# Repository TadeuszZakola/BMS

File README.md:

#Battery Management System  🔋⚡️

Welcome to the Battery Management System (BMS) project! 🚀 This open-source project combines cutting-edge hardware and software to deliver a robust, customizable solution for managing battery packs in applications like electric vehicles. With advanced monitoring, safety features, and seamless integration, this BMS ensures optimal battery performance and longevity. 🌱

🌟 Key Features

26 Individual Cell-Group Voltage Measurements ✅: Monitors voltage across 26 cell groups with high precision.

16 Temperature Sensors 🌡️: Provides comprehensive thermal monitoring to prevent overheating and ensure safe operation.

Cell Balancing 🔄: Actively balances cells to optimize capacity and extend battery lifespan.

Safety Relay 🔒: Isolates the battery pack during faults for enhanced safety.

Current Sensor ⚡: Enables real-time current monitoring and protection against overcurrent conditions.

CAN Bus 📊: Supports CAN communication for integration with external systems and data logging.

Advanced Safety Features 🛡️:

Over-voltage and under-voltage protection

Over-temperature shutdown

Current limiting via relay and BMS logic

Emergency cut-off for driver safety

Hardware & Software Integration 🛠️: Combines robust hardware (microcontroller, sensors, relays) with modular software for real-time monitoring and control.

User-Friendly Dashboard App 🖥️: Visualize battery metrics and configure settings through an intuitive interface.

CAN Integration: Supports CAN bus protocols for data transmission and external control.

Logging: Stores historical data for diagnostics and performance analysis.

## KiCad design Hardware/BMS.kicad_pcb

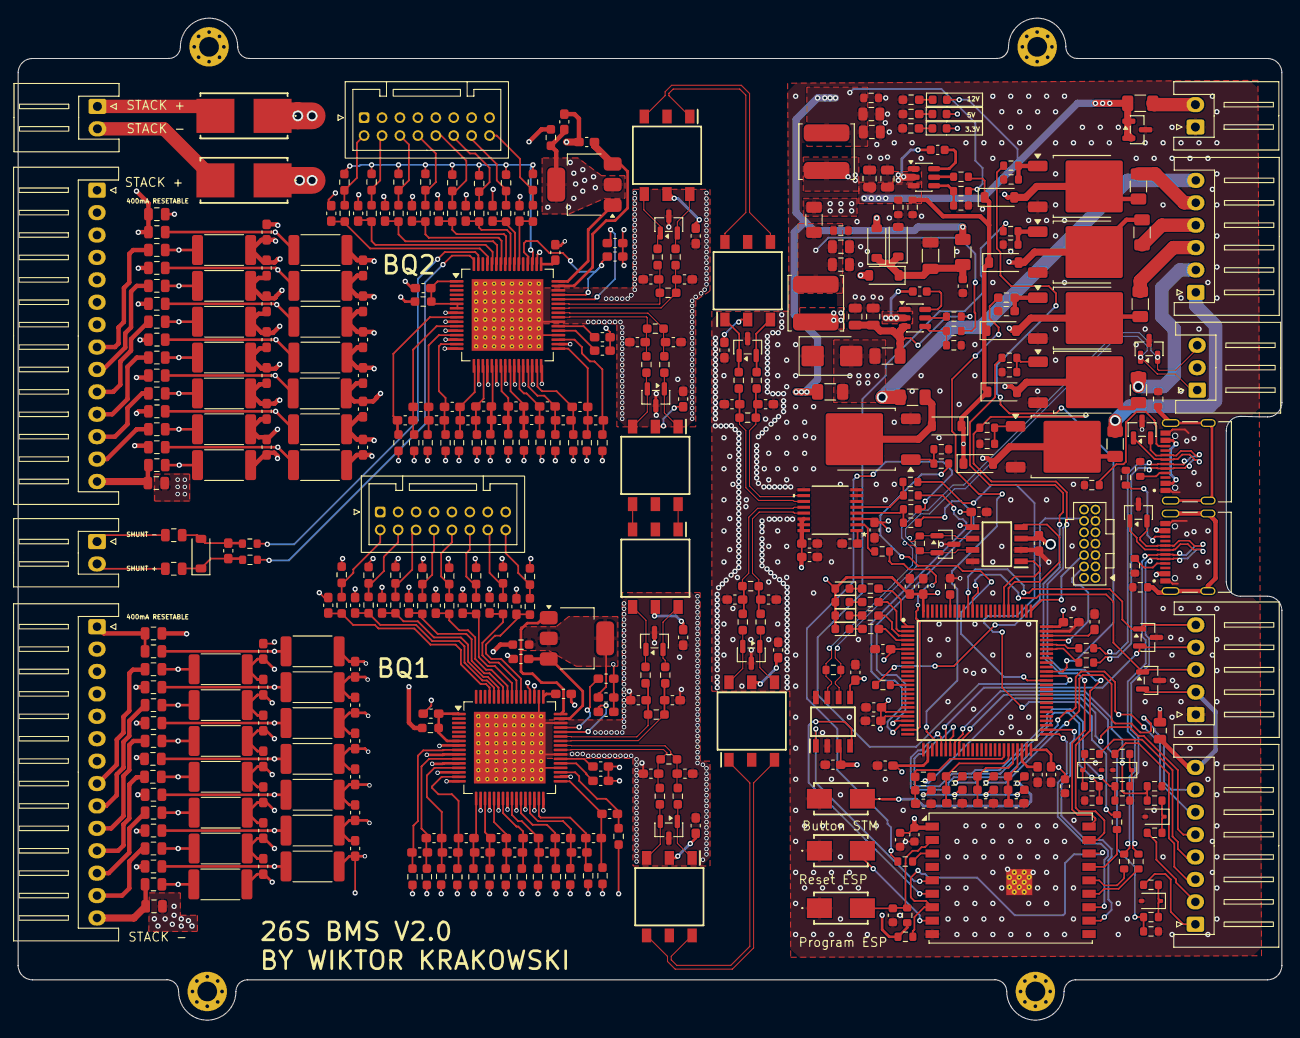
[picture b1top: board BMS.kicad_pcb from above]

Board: 4 copper layers, 141.0 x 111.8 mm, 454 parts (0 on the bottom side), 333 nets.

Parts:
C1: 100n ceramiczny; C_0603_1608Metric_Pad1.08x0.95mm_HandSolder
C2, C51: 0.22uF; C_0603_1608Metric_Pad1.08x0.95mm_HandSolder
C3, C9, C52, C58: 0.1uF; C_0603_1608Metric_Pad1.08x0.95mm_HandSolder
C4, C53: 10nF; C_0603_1608Metric_Pad1.08x0.95mm_HandSolder
C5, C8, C42, C43, C44, C45, C46, C48, C49, C50, C54, C57, C66, C72, C73, C74, C75, C76, C77, C78, C79: 1uF; C_0603_1608Metric_Pad1.08x0.95mm_HandSolder
C6, C55: 4.7uF; C_0603_1608Metric_Pad1.08x0.95mm_HandSolder
C7, C56: 2.2uF; C_0603_1608Metric_Pad1.08x0.95mm_HandSolder
C10, C11, C14, C15, C59, C60, C63, C64, C113, C129, C132, C133, C146, C149, C150, C151, C152, C153: 220p; C_0603_1608Metric_Pad1.08x0.95mm_HandSolder
C16, C17, C18, C19, C20, C21, C22, C23, C24, C25, C26, C27, C28, C29, C30, C31, C32, C33, C34, C35, C36, C37, C38, C39, C40, C41, C80, C81, C82, C83, C84, C85, C86, C87, C88, C89, C90, C91, C92, C93, C94, C95, C96, C97, C98, C99, C100, C101, C102, C103, C104, C105, C145: 0.47uF; C_0603_1608Metric_Pad1.08x0.95mm_HandSolder
C65, C67, C68, C69, C70: 100n; C_0603_1608Metric_Pad1.08x0.95mm_HandSolder
C106, C110, C111, C112, C114: 0.1u; C_0603_1608Metric_Pad1.08x0.95mm_HandSolder
C107, C108: 0.22u; C_0603_1608Metric_Pad1.08x0.95mm_HandSolder
C109: 0.1uF 50V; C_0603_1608Metric_Pad1.08x0.95mm_HandSolder
C116, C117, C147, C148: 100nF; C_0603_1608Metric_Pad1.08x0.95mm_HandSolder
C121, C122: 100n 280mOhm; C_0603_1608Metric
C125: 1uF; C_0603_1608Metric
C126: 22u; C_1206_3216Metric
C130, C131, C136, C154, C155, C157, C160, C161: 22u; C_0805_2012Metric
C134, C135, C137, C156: 1uF; R_0603_1608Metric
C138, C142, C143, C144: 100nF; C_0603_1608Metric
C139, C140: 2.2n; C_0603_1608Metric_Pad1.08x0.95mm_HandSolder
C141: 47n; C_0603_1608Metric_Pad1.08x0.95mm_HandSolder
D1, D8, D11, D13, D19, D20, D21, D22, D23: 60V/0.5/3A; D_SOD-123
D2, D3, D4, D5, D10, D14, D18: LED; LED_0603_1608Metric
D9: 6V; D_SOD-123
D17: P6SMB6.8CA/TR13; D_SMB
D27, D28, D29, D30: 12V; D_SOD-323
D33, D34, D35, D36, D37, D38, D39, D40, D41, D42, D43, D44, D45: 13.3V tvs; SOT-23
F1, F7, F8, F9, F10, F11, F12, F13, F14, F15, F16, F17, F18, F19, F20, F21, F22, F23, F24, F25, F26, F27, F28, F29, F30, F31, F32, F33, F34, F35, F36, F37, F45, F46, F55: 400mA; Fuse_0805_2012Metric
F2, F5, F38, F39: 1A; Fuse_1206_3216Metric
F3: 3A; Fuse_1206_3216Metric
F6, F48, F49, F50, F51, F52: 1A 24V; Fuse_1206_3216Metric
F53, F54: 01550900M
H1, H2, H3, H4: MountingHole; MountingHole_2.2mm_M2_Pad_Via
IC1: STM32H742VIT6
IC2, IC3: TPS563200DDCR; SOT-23-6
J1, J11: Conn_01x02; JST_XH_S2B-XH-A_1x02_P2.50mm_Horizontal
J7: FTSH-107-01-L-D-K; FTSH-107-XX-YYY-D-K
J12, J13: TYPE-C-31-M-12; HRO_TYPE-C-31-M-12
J14, J15: Conn_01x14; JST_XH_S14B-XH-A_1x14_P2.50mm_Horizontal
J17: S2B-XH-A(LF)(SN); JST_XH_S2B-XH-A_1x02_P2.50mm_Horizontal
J19, J25: B16B-PUDSS-1(LF)(SN); JST_PUD_B16B-PUDSS_2x08_P2.00mm_Vertical
J21: S6B-XH-A-1(LF)(SN); JST_XH_S6B-XH-A_1x06_P2.50mm_Horizontal
J22: S3B-XH-A(LF)(SN); JST_XH_S3B-XH-A_1x03_P2.50mm_Horizontal
J23: S8B-XH-A(LF)(SN); JST_XH_S8B-XH-A_1x08_P2.50mm_Horizontal
J24: S5B-XH-A(LF)(SN); JST_XH_S5B-XH-A_1x05_P2.50mm_Horizontal
L1: 4.7u; L_TDK_VLS6045EX_VLS6045AF
L2: 3.3u; L_TDK_VLS6045EX_VLS6045AF
Q1, Q3, Q4, Q5, Q6, Q7: STD3NK90ZT4; TO-252-2
Q2, Q8: 100V/2W; SOT-223-3_TabPin2
R1: 100k; R_0603_1608Metric_Pad0.98x0.95mm_HandSolder
R2, R64: 300; R_0603_1608Metric_Pad0.98x0.95mm_HandSolder
R3, R58, R62, R132, R134: 100; R_0603_1608Metric
R4, R66: 30; R_0603_1608Metric_Pad0.98x0.95mm_HandSolder
R5, R8, R9, R10, R11, R12, R18, R50, R51, R52, R57, R67, R70, R74, R95, R96, R97, R98, R99, R106, R107, R108, R151, R152, R153, R154, R155, R162: 1k; R_0603_1608Metric_Pad0.98x0.95mm_HandSolder
R6, R7, R13, R16, R60, R63, R65, R68, R69, R71, R72, R73: 49; R_0603_1608Metric_Pad0.98x0.95mm_HandSolder
R14, R17, R47, R48, R49, R53, R54, R55, R100, R102, R103, R104, R105, R109, R110, R111, R146, R150, R157, R159: 10k; R_0603_1608Metric_Pad0.98x0.95mm_HandSolder
R15, R61: 300R; R_0603_1608Metric
R19, R20, R21, R22, R23, R24, R25, R26, R27, R28, R29, R30, R31, R32, R112, R113, R114, R115, R116, R117, R118, R119, R120, R121, R122, R123, R124, R125, R161: 100; R_0603_1608Metric_Pad0.98x0.95mm_HandSolder
R33, R34, R35, R36, R37, R38, R39, R40, R41, R42, R43, R44, R45, R46, R77, R78, R79, R80, R81, R82, R83, R84, R85, R86, R87, R88, R89, R90: 20R 2W; R_2512_6332Metric
R56, R59, R131, R133, R135, R168, R169, R170, R172, R173, R179: 10k; R_0603_1608Metric
R75, R76, R101, R126: 5.1K; R_0603_1608Metric
R91, R92, R93, R94, R127, R128, R129, R130: 0R; R_0603_1608Metric
R145, R149, R156, R158: 500; R_0603_1608Metric_Pad0.98x0.95mm_HandSolder
R160, R185, R188, R191: 500; R_0603_1608Metric
R163: 4.7k; R_0603_1608Metric_Pad0.98x0.95mm_HandSolder
R164: 3k; R_0603_1608Metric_Pad0.98x0.95mm_HandSolder
R165: 54.9k; R_0603_1608Metric
R166, R183, R186, R189: 15k; R_0603_1608Metric
R167: 33.2; R_0603_1608Metric
R171, R174: 1M; R_0603_1608Metric
R175, R176, R177, R178: 33; R_0603_1608Metric
R180, R181: 120R; R_0603_1608Metric
R182, R184, R187, R190: 5.6k; R_0603_1608Metric
SW1, SW2, SW3: SW_Push; 1478732
T3, T4, T5, T6, T7, T8: SM91502ALE; SOP254P927X572-6N
U1, U2: BQ79614PAPRQ1; Texas_TQFP-64-1EP_10x10mm_P0.5mm_EP8x8mm_Mask4.44x4.44mm_Th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
U3: PBQ79600PWQ1; BQ79600-Q1
U4, U6: MCP2542FD-E/MF; SOIC127P600X175-8N
U5: ESP32-C3-WROOM-02U

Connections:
5V_USB: C125.2, C126.2, D9.1 (K), D19.1 (K), D20.1 (K), F38.1
12V_IN: F3.1, J17.2
+3.3V: C1.2, C65.2, C66.1, C67.2, C68.1, C69.1, C70.1, C106.1, C116.2, C138.2, C141.2, C142.2, C143.2, C147.2, D2.2 (A), D3.2 (A), D4.2 (A), D5.2 (A), D14.2 (A), F5.2, IC1.6 (VBAT), IC1.20 (VREF+), IC1.21 (VDDA), IC1.27 (VDD_2), IC1.50 (VDD_3), IC1.75 (VDD_4), IC1.100 (VDD_5), J7.3, R146.1, R150.1, R157.1, R159.1, R172.2, R173.2, U3.3 (VIO), U4.5 (VIO), U5.1 (3V3), U6.5 (VIO)
+5V: C108.1, C109.1, C117.1, C148.1, D10.2 (A), D17.2 (A2), F2.2, F39.1, U3.14 (CVDD), U3.15 (BAT), U3.16 (INH), U4.3 (VDD), U6.3 (VDD)
+12V: C134.1, C135.1, C155.1, C157.1, D1.1 (K), D8.1 (K), D13.1 (K), D18.2 (A), D21.1 (K), D22.1 (K), D23.1 (K), D44.1 (A1), D44.2 (A2), F3.2, F55.2, IC2.3 (VIN), R170.2
/12V_Enable: IC1.29 (PA5), R161.1
/Analog_Input1: IC1.30 (PA6), R166.1, R182.2
/Analog_Input2: IC1.32 (PC4), R183.1, R184.2
/Analog_Input3: IC1.33 (PC5), R186.1, R187.2
/Analog_Input4: IC1.34 (PB0), R189.1, R190.2
/Button1: C110.2, IC1.47 (PB11), R145.2, R146.2
/Button2: C111.2, IC1.46 (PB10), R149.2, R150.2
/Button3: C112.2, IC1.45 (PE15), R156.2, R157.2
/Button4: C114.2, IC1.44 (PE14), R158.2, R159.2
/CAN_RX: IC1.81 (PD0), U4.4 (RXD)
/CAN_TX: IC1.82 (PD1), U4.1 (TXD)
/Connectivity/5V_fused_minus: F6.2, J21.3
/Connectivity/12V_Analog_Input1: J23.4, R160.2
/Connectivity/12V_Analog_Input2: J23.3, R185.2
/Connectivity/12V_Analog_Input3: J23.2, R188.2
/Connectivity/12V_Analog_Input4: J23.1, R191.2
/Connectivity/+12V_curr_sense: D33.2 (A2), F55.1, J23.8, J24.2
/Connectivity/B2_IN: J23.7, R149.1
/Connectivity/B3_IN: J23.6, R156.1
/Connectivity/B4_IN: J23.5, R158.1
/Connectivity/D1: D1.2 (A), F49.1, Q1.2 (D)
/Connectivity/D2: D13.2 (A), F48.1, Q3.2 (D)
/Connectivity/D3: D8.2 (A), F6.1, Q4.2 (D)
/Connectivity/EX_CANFD+: D35.2 (A2), D37.2 (A2), J22.3, R180.2, R181.2, U4.7 (CANH), U6.7 (CANH)
/Connectivity/EX_CANFD-: D35.1 (A1), D37.1 (A1), J22.1, R180.1, R181.1, U4.6 (CANL), U6.6 (CANL)
/Connectivity/G1: Q1.1 (G), R3.2, R56.2
/Connectivity/G2: Q3.1 (G), R58.2, R59.2
/Connectivity/PreCharge_OUT: F48.2, J21.5
/Connectivity/Program_esp: C144.2, R173.1, SW3.2, U5.2 (EN)
/Connectivity/Relay_OUT: F49.2, J21.4
/Connectivity/Relay_OUT2: F51.2, J21.2
/Connectivity/Relay_OUT3: F52.2, J21.1
/Connectivity/Relay_OUT4: F50.2, J21.6
/Connectivity/USB1_DN: D34.1 (A1), J12.A7 (DN1), J12.B7 (DN2), R176.2
/Connectivity/USB1_DP: D34.2 (A2), J12.A6 (DP1), J12.B6 (DP2), R175.2
/Connectivity/USB2+: R177.1, U5.14 (IO19)
/Connectivity/USB2-: R178.1, U5.13 (IO18)
/Connectivity/USB2_DN: D36.1 (A1), J13.A7 (DN1), J13.B7 (DN2), R178.2
/Connectivity/USB2_DP: D36.2 (A2), J13.A6 (DP1), J13.B6 (DP2), R177.2
/Connectivity/esp32_can_rx: U5.6 (IO7), U6.4 (RXD)
/Connectivity/esp32_can_tx: U5.5 (IO6), U6.1 (TXD)
/Connectivity/relay_enable1: R62.1, U5.18 (IO0)
/Connectivity/relay_enable2: R132.1, U5.17 (IO1)
/ERROR: IC1.1 (PE2), R154.1
/LED1: IC1.2 (PE3), R153.1
/LED2: IC1.3 (PE4), R152.1
/LED3: IC1.4 (PE5), R151.1
/Mesurements_LTC1/Bat_pin: C4.2, R4.2, U1.1 (BAT), U1.6 (CB14), U1.7 (VC14)
/Mesurements_LTC1/Battery/Batt1_+: F21.2, R2.1, R4.1
/Mesurements_LTC1/CB0: C41.1, R46.2, U1.34 (CB0)
/Mesurements_LTC1/CB1: C40.1, C41.2, R45.2, U1.32 (CB1)
/Mesurements_LTC1/CB2: C39.1, C40.2, R44.2, U1.30 (CB2)
/Mesurements_LTC1/CB3: C38.1, C39.2, R43.2, U1.28 (CB3)
/Mesurements_LTC1/CB4: C37.1, C38.2, R42.2, U1.26 (CB4)
/Mesurements_LTC1/CB5: C36.1, C37.2, R41.2, U1.24 (CB5)
/Mesurements_LTC1/CB6: C35.1, C36.2, R40.2, U1.22 (CB6)
/Mesurements_LTC1/CB7: C34.1, C35.2, R39.2, U1.20 (CB7)
/Mesurements_LTC1/CB8: C33.1, C34.2, R38.2, U1.18 (CB8)
/Mesurements_LTC1/CB9: C32.1, C33.2, R37.2, U1.16 (CB9)
/Mesurements_LTC1/CB10: C31.1, C32.2, R36.2, U1.14 (CB10)
/Mesurements_LTC1/CB11: C30.1, C31.2, R35.2, U1.12 (CB11)
/Mesurements_LTC1/CB12: C29.1, C30.2, R34.2, U1.10 (CB12)
/Mesurements_LTC1/CB13: C29.2, R33.2, U1.8 (CB13)
/Mesurements_LTC1/COMHN: C60.2, R67.2, R71.1, U1.42 (COMHN)
/Mesurements_LTC1/COMHP: C59.2, R67.1, R68.1, U1.43 (COMHP)
/Mesurements_LTC1/COMLN: C133.2, R65.2, R70.2, U1.41 (COMLN)
/Mesurements_LTC1/COMLP: C132.2, R69.2, R70.1, U1.40 (COMLP)
/Mesurements_LTC1/Temperature_LTC_1/T1: C42.1, R8.1, U1.61 (GPIO1)
/Mesurements_LTC1/Temperature_LTC_1/T2: C45.1, R11.1, U1.60 (GPIO2)
/Mesurements_LTC1/Temperature_LTC_1/T3: C46.1, R12.1, U1.59 (GPIO3)
/Mesurements_LTC1/Temperature_LTC_1/T4: C43.1, R9.1, U1.58 (GPIO4)
/Mesurements_LTC1/Temperature_LTC_1/T5: C44.1, R10.1, U1.57 (GPIO5)
/Mesurements_LTC1/Temperature_LTC_1/T6: C48.1, R50.1, U1.56 (GPIO6)
/Mesurements_LTC1/Temperature_LTC_1/T7: C49.1, R51.1, U1.55 (GPIO7)
/Mesurements_LTC1/Temperature_LTC_1/T8: C50.1, R52.1, U1.54 (GPIO8)
/Mesurements_LTC1/Temperature_LTC_1/TSREF: R14.1, R17.2, R47.2, R48.2, R49.2, R53.2, R54.2, R55.2, U1.51 (TSREF)
/Mesurements_LTC1/Temperature_LTC_1/Thermistor1: J19.2, R8.2, R14.2
/Mesurements_LTC1/Temperature_LTC_1/Thermistor2: J19.4, R11.2, R48.1
/Mesurements_LTC1/Temperature_LTC_1/Thermistor3: J19.6, R12.2, R49.1
/Mesurements_LTC1/Temperature_LTC_1/Thermistor4: J19.8, R9.2, R17.1
/Mesurements_LTC1/Temperature_LTC_1/Thermistor5: J19.10, R10.2, R47.1
/Mesurements_LTC1/Temperature_LTC_1/Thermistor6: J19.12, R50.2, R53.1
/Mesurements_LTC1/Temperature_LTC_1/Thermistor7: J19.14, R51.2, R54.1
/Mesurements_LTC1/Temperature_LTC_1/Thermistor8: J19.16, R52.2, R55.1
/Mesurements_LTC1/VC0: C28.1, R19.2, U1.35 (VC0)
/Mesurements_LTC1/VC1: C27.1, C28.2, R32.2, U1.33 (VC1)
/Mesurements_LTC1/VC2: C26.1, C27.2, R31.2, U1.31 (VC2)
/Mesurements_LTC1/VC3: C25.1, C26.2, R30.2, U1.29 (VC3)
/Mesurements_LTC1/VC4: C24.1, C25.2, R29.2, U1.27 (VC4)
/Mesurements_LTC1/VC5: C23.1, C24.2, R28.2, U1.25 (VC5)
/Mesurements_LTC1/VC6: C22.1, C23.2, R27.2, U1.23 (VC6)
/Mesurements_LTC1/VC7: C21.1, C22.2, R26.2, U1.21 (VC7)
/Mesurements_LTC1/VC8: C20.1, C21.2, R25.2, U1.19 (VC8)
/Mesurements_LTC1/VC9: C19.1, C20.2, R24.2, U1.17 (VC9)
/Mesurements_LTC1/VC10: C18.1, C19.2, R23.2, U1.15 (VC10)
/Mesurements_LTC1/VC11: C17.1, C18.2, R22.2, U1.13 (VC11)
/Mesurements_LTC1/VC12: C16.1, C17.2, R21.2, U1.11 (VC12)
/Mesurements_LTC1/VC13: C16.2, R20.2, U1.9 (VC13)
/Mesurements_LTC1/to_rx: C6.2, U1.45 (CVDD), U1.52 (RX)
/Mesurements_LTC2/Battery2/Batt2_+: F23.2, R64.1, R66.1
/Mesurements_LTC2/CB0: C105.1, R90.2, U2.34 (CB0)
/Mesurements_LTC2/CB1: C104.1, C105.2, R89.2, U2.32 (CB1)
/Mesurements_LTC2/CB2: C103.1, C104.2, R88.2, U2.30 (CB2)
/Mesurements_LTC2/CB3: C102.1, C103.2, R87.2, U2.28 (CB3)
/Mesurements_LTC2/CB4: C101.1, C102.2, R86.2, U2.26 (CB4)
/Mesurements_LTC2/CB5: C100.1, C101.2, R85.2, U2.24 (CB5)
/Mesurements_LTC2/CB6: C99.1, C100.2, R84.2, U2.22 (CB6)
/Mesurements_LTC2/CB7: C98.1, C99.2, R83.2, U2.20 (CB7)
/Mesurements_LTC2/CB8: C97.1, C98.2, R82.2, U2.18 (CB8)
/Mesurements_LTC2/CB9: C96.1, C97.2, R81.2, U2.16 (CB9)
/Mesurements_LTC2/CB10: C95.1, C96.2, R80.2, U2.14 (CB10)
/Mesurements_LTC2/CB11: C94.1, C95.2, R79.2, U2.12 (CB11)
/Mesurements_LTC2/CB12: C93.1, C94.2, R78.2, U2.10 (CB12)
/Mesurements_LTC2/CB13: C93.2, R77.2, U2.8 (CB13)
/Mesurements_LTC2/COMHN: C129.2, R57.2, R63.1, U2.42 (COMHN)
/Mesurements_LTC2/COMHP: C113.2, R57.1, R60.1, U2.43 (COMHP)
/Mesurements_LTC2/COMLN: C15.2, R13.2, R18.2, U2.41 (COMLN)
/Mesurements_LTC2/COMLP: C14.2, R16.2, R18.1, U2.40 (COMLP)
/Mesurements_LTC2/Temperature_LTC_2/T1: C72.1, R95.1, U2.61 (GPIO1)
/Mesurements_LTC2/Temperature_LTC_2/T2: C75.1, R98.1, U2.60 (GPIO2)
/Mesurements_LTC2/Temperature_LTC_2/T3: C76.1, R99.1, U2.59 (GPIO3)
/Mesurements_LTC2/Temperature_LTC_2/T4: C73.1, R96.1, U2.58 (GPIO4)
/Mesurements_LTC2/Temperature_LTC_2/T5: C74.1, R97.1, U2.57 (GPIO5)
/Mesurements_LTC2/Temperature_LTC_2/T6: C77.1, R106.1, U2.56 (GPIO6)
/Mesurements_LTC2/Temperature_LTC_2/T7: C78.1, R107.1, U2.55 (GPIO7)
/Mesurements_LTC2/Temperature_LTC_2/T8: C79.1, R108.1, U2.54 (GPIO8)
/Mesurements_LTC2/Temperature_LTC_2/TSREF: R100.1, R102.2, R103.2, R104.2, R105.2, R109.2, R110.2, R111.2, U2.51 (TSREF)
/Mesurements_LTC2/Temperature_LTC_2/Thermistor1: J25.2, R95.2, R100.2
/Mesurements_LTC2/Temperature_LTC_2/Thermistor2: J25.4, R98.2, R104.1
/Mesurements_LTC2/Temperature_LTC_2/Thermistor3: J25.6, R99.2, R105.1
/Mesurements_LTC2/Temperature_LTC_2/Thermistor4: J25.8, R96.2, R102.1
/Mesurements_LTC2/Temperature_LTC_2/Thermistor5: J25.10, R97.2, R103.1
/Mesurements_LTC2/Temperature_LTC_2/Thermistor6: J25.12, R106.2, R109.1
/Mesurements_LTC2/Temperature_LTC_2/Thermistor7: J25.14, R107.2, R110.1
/Mesurements_LTC2/Temperature_LTC_2/Thermistor8: J25.16, R108.2, R111.1
/Mesurements_LTC2/VC0: C92.1, R112.2, U2.35 (VC0)
/Mesurements_LTC2/VC1: C91.1, C92.2, R125.2, U2.33 (VC1)
/Mesurements_LTC2/VC2: C90.1, C91.2, R124.2, U2.31 (VC2)
/Mesurements_LTC2/VC3: C89.1, C90.2, R123.2, U2.29 (VC3)
/Mesurements_LTC2/VC4: C88.1, C89.2, R122.2, U2.27 (VC4)
/Mesurements_LTC2/VC5: C87.1, C88.2, R121.2, U2.25 (VC5)
/Mesurements_LTC2/VC6: C86.1, C87.2, R120.2, U2.23 (VC6)
/Mesurements_LTC2/VC7: C85.1, C86.2, R119.2, U2.21 (VC7)
/Mesurements_LTC2/VC8: C84.1, C85.2, R118.2, U2.19 (VC8)
/Mesurements_LTC2/VC9: C83.1, C84.2, R117.2, U2.17 (VC9)
/Mesurements_LTC2/VC10: C82.1, C83.2, R116.2, U2.15 (VC10)
/Mesurements_LTC2/VC11: C81.1, C82.2, R115.2, U2.13 (VC11)
/Mesurements_LTC2/VC12: C80.1, C81.2, R114.2, U2.11 (VC12)
/Mesurements_LTC2/VC13: C80.2, R113.2, U2.9 (VC13)
/Mesurements_LTC2/to_rx: C55.2, U2.45 (CVDD), U2.52 (RX)
/NFAULT: IC1.24 (PA2), R93.2
/NRST: J7.12, R94.2
/Power/5V/5V_unfused: C136.1, C154.1, C156.1, F2.1, F38.2, L1.2, R165.2
/Power/Power_3.3V/3.3V_unfused: C130.1, C131.1, C137.1, F5.1, L2.2, R167.2
/RX_1: IC1.23 (PA1), R91.2
/SIGNAL_PRECHARGE: IC1.65 (PC8), R58.1
/SIGNAL_RELAY: IC1.64 (PC7), R3.1
/SIGNAL_RELAY2: IC1.63 (PC6), R134.1
/SPI_CLK: D33.1 (A1), IC1.89 (PB3), J24.3
/SPI_MISO: D45.1 (A1), IC1.90 (PB4), J24.5
/SPI_MOSI: D45.2 (A2), IC1.31 (PA7), J24.4
/STM Comunication Interface/COMHN: C11.2, R5.2, R7.1, U3.12 (COMHN)
/STM Comunication Interface/COMHP: C10.2, R5.1, R6.1, U3.13 (COMHP)
/STM Comunication Interface/COMLN: C64.2, R72.2, R74.2, U3.11 (COMLN)
/STM Comunication Interface/COMLP: C63.2, R73.2, R74.1, U3.10 (COMLP)
/STM Comunication Interface/MISO/TX: R91.1, R127.1, U3.5 (MISO/TX)
/STM Comunication Interface/MOSI/RX: R92.1, R128.1, U3.4 (MOSI/RX)
/STM Comunication Interface/NFAULT: R93.1, U3.2 (NFAULT)
/SWCLK: IC1.76 (PA14), J7.6
/SWDIO: IC1.72 (PA13), J7.4
/TX_1: IC1.22 (PA0), R92.2
/UART2_RX: IC1.51 (PB12), U5.12 (IO21/TXD)
/UART2_TX: IC1.52 (PB13), U5.11 (IO20/RXD)
/USB+: IC1.71 (PA12), R175.1
/USB-: IC1.70 (PA11), R176.1
/esp32_RX2: R127.2, R129.2
/esp32_TX2: R128.2, R130.2
/galvanic_isulation_0/S1+: D42.1 (A1), R68.2, T3.4 (SEC_1)
/galvanic_isulation_0/S1-: D42.2 (A2), R71.2, T3.6 (SEC_3)
/galvanic_isulation_0/S2+: T3.3 (PRI_3), T4.4 (SEC_1)
/galvanic_isulation_0/S2-: T3.1 (PRI_1), T4.6 (SEC_3)
/galvanic_isulation_0/S3+: D43.2 (A2), R73.1, T4.3 (PRI_3)
/galvanic_isulation_0/S3-: D43.1 (A1), R72.1, T4.1 (PRI_1)
/galvanic_isulation_1/S1+: D38.1 (A1), R60.2, T5.4 (SEC_1)
/galvanic_isulation_1/S1-: D38.2 (A2), R63.2, T5.6 (SEC_3)
/galvanic_isulation_1/S2+: T5.3 (PRI_3), T6.4 (SEC_1)
/galvanic_isulation_1/S2-: T5.1 (PRI_1), T6.6 (SEC_3)
/galvanic_isulation_1/S3+: D39.2 (A2), R69.1, T6.3 (PRI_3)
/galvanic_isulation_1/S3-: D39.1 (A1), R65.1, T6.1 (PRI_1)
/galvanic_isulation_2/S1+: D40.1 (A1), R6.2, T7.4 (SEC_1)
/galvanic_isulation_2/S1-: D40.2 (A2), R7.2, T7.6 (SEC_3)
/galvanic_isulation_2/S2+: T7.3 (PRI_3), T8.4 (SEC_1)
/galvanic_isulation_2/S2-: T7.1 (PRI_1), T8.6 (SEC_3)
/galvanic_isulation_2/S3+: D41.2 (A2), R16.1, T8.3 (PRI_3)
/galvanic_isulation_2/S3-: D41.1 (A1), R13.1, T8.1 (PRI_1)
Batt_Coupling: C2.1, C3.1, C4.1, C5.1, C6.1, C7.1, C8.1, C9.1, C42.2, C43.2, C44.2, C45.2, C46.2, C48.2, C49.2, C50.2, C59.1, C60.1, C132.1, C133.1, C146.2, C150.2, D39.3 (common), D42.3 (common), F20.2, J19.1, J19.3, J19.5, J19.7, J19.9, J19.11, J19.13, J19.15, U1.36 (REFHM), U1.39 (AVSS), U1.46 (CVSS), U1.50 (DVSS), U1.65 (PAD)
GND: C1.1, C10.1, C11.1, C63.1, C64.1, C65.1, C66.2, C67.1, C68.2, C69.2, C70.2, C106.2, C107.1, C108.2, C109.2, C110.1, C111.1, C112.1, C114.1, C116.1, C117.2, C125.1, C126.1, C130.2, C131.2, C134.2, C135.2, C136.2, C137.2, C138.1, C139.1, C140.1, C141.1, C142.1, C143.1, C144.1, C147.1, C148.2, C149.2, C152.1, C154.2, C155.2, C156.2, C157.2, C160.2, C161.2, D9.2 (A), D17.1 (A1), D27.2 (A), D28.2 (A), D29.2 (A), D30.2 (A), D33.3 (common), D34.3 (common), D35.3 (common), D36.3 (common), D37.3 (common), D40.3 (common), D43.3 (common), D44.3 (common), D45.3 (common), IC1.19 (VSSA), IC1.26 (VSS_2), IC1.49 (VSS_3), IC1.74 (VSS_4), IC1.99 (VSS_5), IC2.1 (GND), IC3.1 (GND), J7.5, J7.7, J7.11, J12.A1_B12 (GND), J12.B1_A12 (GND), J13.A1_B12 (GND), J13.B1_A12 (GND), J17.1, J24.1, Q1.3 (S), Q3.3 (S), Q4.3 (S), Q5.3 (S), Q6.3 (S), Q7.3 (S), R1.1, R56.1, R59.1, R75.1, R76.2, R101.2, R126.1, R131.1, R133.1, R135.1, R155.1, R162.1, R163.1, R164.1, R168.1, R169.1, R171.1, R174.1, R182.1, R184.1, R187.1, R190.1, SW1.2, SW2.1, SW3.1, U3.6 (SCLK), U3.7 (nCS), U3.8 (nUART/SPI(SPI_RDY)), U3.9 (GND), U4.2 (VSS), U4.8 (STBY), U5.9 (GND), U5.19 (GND), U6.2 (VSS), U6.8 (STBY)
GND_HV2: C14.1, C15.1, C51.1, C52.1, C53.1, C54.1, C55.1, C56.1, C57.1, C58.1, C72.2, C73.2, C74.2, C75.2, C76.2, C77.2, C78.2, C79.2, C113.1, C129.1, C151.1, C153.2, D38.3 (common), D41.3 (common), F22.2, J25.1, J25.3, J25.5, J25.7, J25.9, J25.11, J25.13, J25.15, U2.36 (REFHM), U2.39 (AVSS), U2.46 (CVSS), U2.50 (DVSS), U2.65 (PAD)
unnamed: D2.1 (K), R151.2
unnamed: D3.1 (K), R152.2
unnamed: D4.1 (K), R153.2
unnamed: D5.1 (K), R154.2
unnamed: D10.1 (K), R155.2
unnamed: C145.1, D11.2 (A), F46.2, R61.2
unnamed: C145.2, D11.1 (K), F45.2, R15.2
unnamed: D14.1 (K), R162.2
unnamed: D18.1 (K), R164.2
unnamed: D19.2 (A), J13.A4_B9 (VBUS), J13.B4_A9 (VBUS)
unnamed: D20.2 (A), J12.A4_B9 (VBUS), J12.B4_A9 (VBUS)
unnamed: D21.2 (A), F51.1, Q5.2 (D)
unnamed: D22.2 (A), F52.1, Q6.2 (D)
unnamed: D23.2 (A), F50.1, Q7.2 (D)
unnamed: D27.1 (K), R160.1, R166.2
unnamed: D28.1 (K), R183.2, R185.1
unnamed: D29.1 (K), R186.2, R188.1
unnamed: D30.1 (K), R189.2, R191.1
unnamed: F1.2, R20.1, R33.1
unnamed: F7.2, R21.1, R34.1
unnamed: F8.2, R22.1, R35.1
unnamed: F9.2, R23.1, R36.1
unnamed: F10.2, R24.1, R37.1
unnamed: F11.2, R25.1, R38.1
unnamed: F12.2, R26.1, R39.1
unnamed: F13.2, R27.1, R40.1
unnamed: F14.2, R28.1, R41.1
unnamed: F15.2, R29.1, R42.1
unnamed: F16.2, R30.1, R43.1
unnamed: F17.2, R31.1, R44.1
unnamed: F18.2, R32.1, R45.1
unnamed: F19.2, R19.1, R46.1
unnamed: F24.2, R77.1, R113.1
unnamed: F25.2, R78.1, R114.1
unnamed: F26.2, R79.1, R115.1
unnamed: F27.2, R80.1, R116.1
unnamed: F28.2, R81.1, R117.1
unnamed: F29.2, R82.1, R118.1
unnamed: F30.2, R83.1, R119.1
unnamed: F31.2, R84.1, R120.1
unnamed: F32.2, R85.1, R121.1
unnamed: F33.2, R86.1, R122.1
unnamed: F34.2, R87.1, R123.1
unnamed: F35.2, R88.1, R124.1
unnamed: F36.2, R89.1, R125.1
unnamed: F37.2, R90.1, R112.1
unnamed: IC1.94 (BOOT0), R1.2
unnamed: IC1.14 (NRST), R94.1
unnamed: C139.2, IC1.48 (VCAP_1)
unnamed: C140.2, IC1.73 (VCAP_2)
unnamed: IC2.5 (EN), R170.1
unnamed: C121.2, IC2.2 (SW), L1.1
unnamed: C121.1, IC2.6 (VBST)
unnamed: IC2.4 (VFB), R165.1, R169.2
unnamed: IC3.5 (EN), R179.1
unnamed: C122.2, IC3.2 (SW), L2.1
unnamed: C122.1, IC3.6 (VBST)
unnamed: IC3.4 (VFB), R167.1, R168.2
unnamed: C160.1, C161.1, F39.2, IC3.3 (VIN), R179.2
unnamed: F53.2, J1.1
unnamed: F54.2, J1.2
unnamed: F46.1, J11.1
unnamed: F45.1, J11.2
unnamed: J12.A5 (CC1), R76.1
unnamed: J12.B5 (CC2), R75.2
unnamed: J12.S1 (SHIELD), J12.S2 (SHIELD), J12.S3 (SHIELD), J12.S4 (SHIELD), R174.2
unnamed: J13.A5 (CC1), R101.1
unnamed: J13.B5 (CC2), R126.2
unnamed: J13.S1 (SHIELD), J13.S2 (SHIELD), J13.S3 (SHIELD), J13.S4 (SHIELD), R171.2
unnamed: F7.1, J14.2
unnamed: F8.1, J14.3
unnamed: F9.1, J14.4
unnamed: F10.1, J14.5
unnamed: F11.1, J14.6
unnamed: F12.1, J14.7
unnamed: F13.1, J14.8
unnamed: F14.1, J14.9
unnamed: F15.1, J14.10
unnamed: F16.1, J14.11
unnamed: F17.1, J14.12
unnamed: F18.1, J14.13
unnamed: F19.1, F20.1, J14.14
unnamed: F23.1, F24.1, J15.1
unnamed: F25.1, J15.2
unnamed: F26.1, J15.3
unnamed: F27.1, J15.4
unnamed: F28.1, J15.5
unnamed: F29.1, J15.6
unnamed: F30.1, J15.7
unnamed: F31.1, J15.8
unnamed: F32.1, J15.9
unnamed: F33.1, J15.10
unnamed: F34.1, J15.11
unnamed: F35.1, J15.12
unnamed: F36.1, J15.13
unnamed: Q2.1 (B), U2.48 (NPNB)
unnamed: C51.2, Q2.2 (C), R64.2
unnamed: C52.2, Q2.3 (E), U2.47 (LDOIN)
unnamed: Q4.1 (G), R161.2, R163.2
unnamed: Q5.1 (G), R62.2, R131.2
unnamed: Q6.1 (G), R132.2, R133.2
unnamed: Q7.1 (G), R134.2, R135.2
unnamed: Q8.1 (B), U1.48 (NPNB)
unnamed: C2.2, Q8.2 (C), R2.2
unnamed: C3.2, Q8.3 (E), U1.47 (LDOIN)
unnamed: R145.1, SW1.1
unnamed: C146.1, T3.5 (SEC_2)
unnamed: C149.1, T4.2 (PRI_2)
unnamed: C151.2, T5.5 (SEC_2)
unnamed: C150.1, T6.2 (PRI_2)
unnamed: C152.2, T7.5 (SEC_2)
unnamed: C153.1, T8.2 (PRI_2)
unnamed: C5.2, U1.38 (AVDD)
unnamed: R61.1, U1.63 (BBN)
unnamed: R15.1, U1.64 (BBP)
unnamed: C7.2, U1.49 (DVDD)
unnamed: C9.2, U1.44 (NEG5V)
unnamed: C8.2, U1.37 (REFHP)
unnamed: C54.2, U2.38 (AVDD)
unnamed: C53.2, R66.2, U2.1 (BAT), U2.7 (VC14)
unnamed: C56.2, U2.49 (DVDD)
unnamed: C58.2, U2.44 (NEG5V)
unnamed: C57.2, U2.37 (REFHP)
unnamed: C107.2, U3.1 (DVDD)
unnamed: R172.1, U5.7 (IO8), U5.16 (IO2)
unnamed: R129.1, U5.15 (IO3)
unnamed: R130.1, U5.3 (IO4)
unnamed: SW2.2, U5.8 (IO9)
Stack+: F1.1, F21.1, F53.1, J14.1
Stack-: F22.1, F37.1, F54.1, J15.14

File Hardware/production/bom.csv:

Designator,Footprint,Quantity,Value,LCSC Part #
C1,0603,1,100n ceramiczny,
"C10, C11, C113, C129, C132, C133, C14, C146, C149, C15, C150, C151, C152, C153, C59, C60, C63, C64",0603,18,220p,
"C100, C101, C102, C103, C104, C105, C145, C16, C17, C18, C19, C20, C21, C22, C23, C24, C25, C26, C27, C28, C29, C30, C31, C32, C33, C34, C35, C36, C37, C38, C39, C40, C41, C80, C81, C82, C83, C84, C85, C86, C87, C88, C89, C90, C91, C92, C93, C94, C95, C96, C97, C98, C99",0603,53,0.47uF,
"C106, C110, C111, C112, C114",0603,5,0.1u,
"C107, C108",0603,2,0.22u,
C109,0603,1,0.1uF 50V,
"C116, C117, C138, C142, C143, C144, C147, C148",0603,8,100nF,
"C121, C122",0603,2,100n 280mOhm,
"C125, C134, C135, C137, C156, C42, C43, C44, C45, C46, C48, C49, C5, C50, C54, C57, C66, C72, C73, C74, C75, C76, C77, C78, C79, C8",0603,26,1uF,
C126,1206,1,22u,
"C130, C131, C136, C154, C155, C157, C160, C161",0805,8,22u,
"C139, C140",0603,2,2.2n,
C141,0603,1,47n,
"C2, C51",0603,2,0.22uF,
"C3, C52, C58, C9",0603,4,0.1uF,
"C4, C53",0603,2,10nF,
"C55, C6",0603,2,4.7uF,
"C56, C7",0603,2,2.2uF,
"C65, C67, C68, C69, C70",0603,5,100n,
"D1, D11, D13, D19, D20, D21, D22, D23, D8",D_SOD-123,9,60V/0.5/3A,
"D10, D14, D18, D2, D3, D4, D5",0603,7,LED,
D17,D_SMB,1,P6SMB6.8CA/TR13,
"D27, D28, D29, D30",D_SOD-323,4,12V,
"D33, D34, D35, D36, D37, D38, D39, D40, D41, D42, D43, D44, D45",SOT-23,13,13.3V tvs,
D9,D_SOD-123,1,6V,
"F1, F10, F11, F12, F13, F14, F15, F16, F17, F18, F19, F20, F21, F22, F23, F24, F25, F26, F27, F28, F29, F30, F31, F32, F33, F34, F35, F36, F37, F45, F46, F55, F7, F8, F9",0805,35,400mA,
"F2, F38, F39, F5",1206,4,1A,
F3,1206,1,3A,
"F48, F49, F50, F51, F52, F6",1206,6,1A 24V,
"F53, F54",01550900M,2,01550900M,
"H1, H2, H3, H4",MountingHole_2.2mm_M2_Pad_Via,4,MountingHole,
IC1,STM32H742VIT6,1,STM32H742VIT6,
"IC2, IC3",SOT-23-6,2,TPS563200DDCR,
"J1, J11",JST_XH_S2B-XH-A_1x02_P2.50mm_Horizontal,2,Conn_01x02,
"J12, J13",HRO_TYPE-C-31-M-12,2,TYPE-C-31-M-12,
"J14, J15",JST_XH_S14B-XH-A_1x14_P2.50mm_Horizontal,2,Conn_01x14,
J17,JST_XH_S2B-XH-A_1x02_P2.50mm_Horizontal,1,S2B-XH-A(LF)(SN),
"J19, J25",JST_PUD_B16B-PUDSS_2x08_P2.00mm_Vertical,2,B16B-PUDSS-1(LF)(SN),
J21,JST_XH_S6B-XH-A_1x06_P2.50mm_Horizontal,1,S6B-XH-A-1(LF)(SN),
J22,JST_XH_S3B-XH-A_1x03_P2.50mm_Horizontal,1,S3B-XH-A(LF)(SN),
J23,JST_XH_S8B-XH-A_1x08_P2.50mm_Horizontal,1,S8B-XH-A(LF)(SN),
J24,JST_XH_S5B-XH-A_1x05_P2.50mm_Horizontal,1,S5B-XH-A(LF)(SN),
J7,FTSH-107-XX-YYY-D-K,1,FTSH-107-01-L-D-K,
L1,L_TDK_VLS6045EX_VLS6045AF,1,4.7u,
L2,L_TDK_VLS6045EX_VLS6045AF,1,3.3u,
"Q1, Q3, Q4, Q5, Q6, Q7",TO-252-2,6,STD3NK90ZT4,
"Q2, Q8",SOT-223-3_TabPin2,2,100V/2W,
R1,0603,1,100k,
"R10, R106, R107, R108, R11, R12, R151, R152, R153, R154, R155, R162, R18, R5, R50, R51, R52, R57, R67, R70, R74, R8, R9, R95, R96, R97, R98, R99",0603,28,1k,
"R100, R102, R103, R104, R105, R109, R110, R111, R131, R133, R135, R14, R146, R150, R157, R159, R168, R169, R17, R170, R172, R173, R179, R47, R48, R49, R53, R54, R55, R56, R59",0603,31,10k,
"R101, R126, R75, R76",0603,4,5.1K,
"R112, R113, R114, R115, R116, R117, R118, R119, R120, R121, R122, R123, R124, R125, R132, R134, R161, R19, R20, R21, R22, R23, R24, R25, R26, R27, R28, R29, R3, R30, R31, R32, R58, R62",0603,34,100,
"R127, R128, R129, R130, R91, R92, R93, R94",0603,8,0R,
"R13, R16, R6, R60, R63, R65, R68, R69, R7, R71, R72, R73",0603,12,49,
"R145, R149, R156, R158, R160, R185, R188, R191",0603,8,500,
"R15, R61",0603,2,300R,
R163,0603,1,4.7k,
R164,0603,1,3k,
R165,0603,1,54.9k,
"R166, R183, R186, R189",0603,4,15k,
R167,0603,1,33.2,
"R171, R174",0603,2,1M,
"R175, R176, R177, R178",0603,4,33,
"R180, R181",0603,2,120R,
"R182, R184, R187, R190",0603,4,5.6k,
"R2, R64",0603,2,300,
"R33, R34, R35, R36, R37, R38, R39, R40, R41, R42, R43, R44, R45, R46, R77, R78, R79, R80, R81, R82, R83, R84, R85, R86, R87, R88, R89, R90",2512,28,20R 2W,
"R4, R66",0603,2,30,
"SW1, SW2, SW3",1478732,3,SW_Push,
"T3, T4, T5, T6, T7, T8",SOP254P927X572-6N,6,SM91502ALE,
"U1, U2",Texas_TQFP-64-1EP_10x10mm_P0.5mm_EP8x8mm_Mask4.44x4.44mm_ThermalVias,2,BQ79614PAPRQ1,
U3,BQ79600-Q1,1,PBQ79600PWQ1,
"U4, U6",SOIC127P600X175-8N,2,MCP2542FD-E/MF,
U5,ESP32-C3-WROOM-02U,1,ESP32-C3-WROOM-02U,

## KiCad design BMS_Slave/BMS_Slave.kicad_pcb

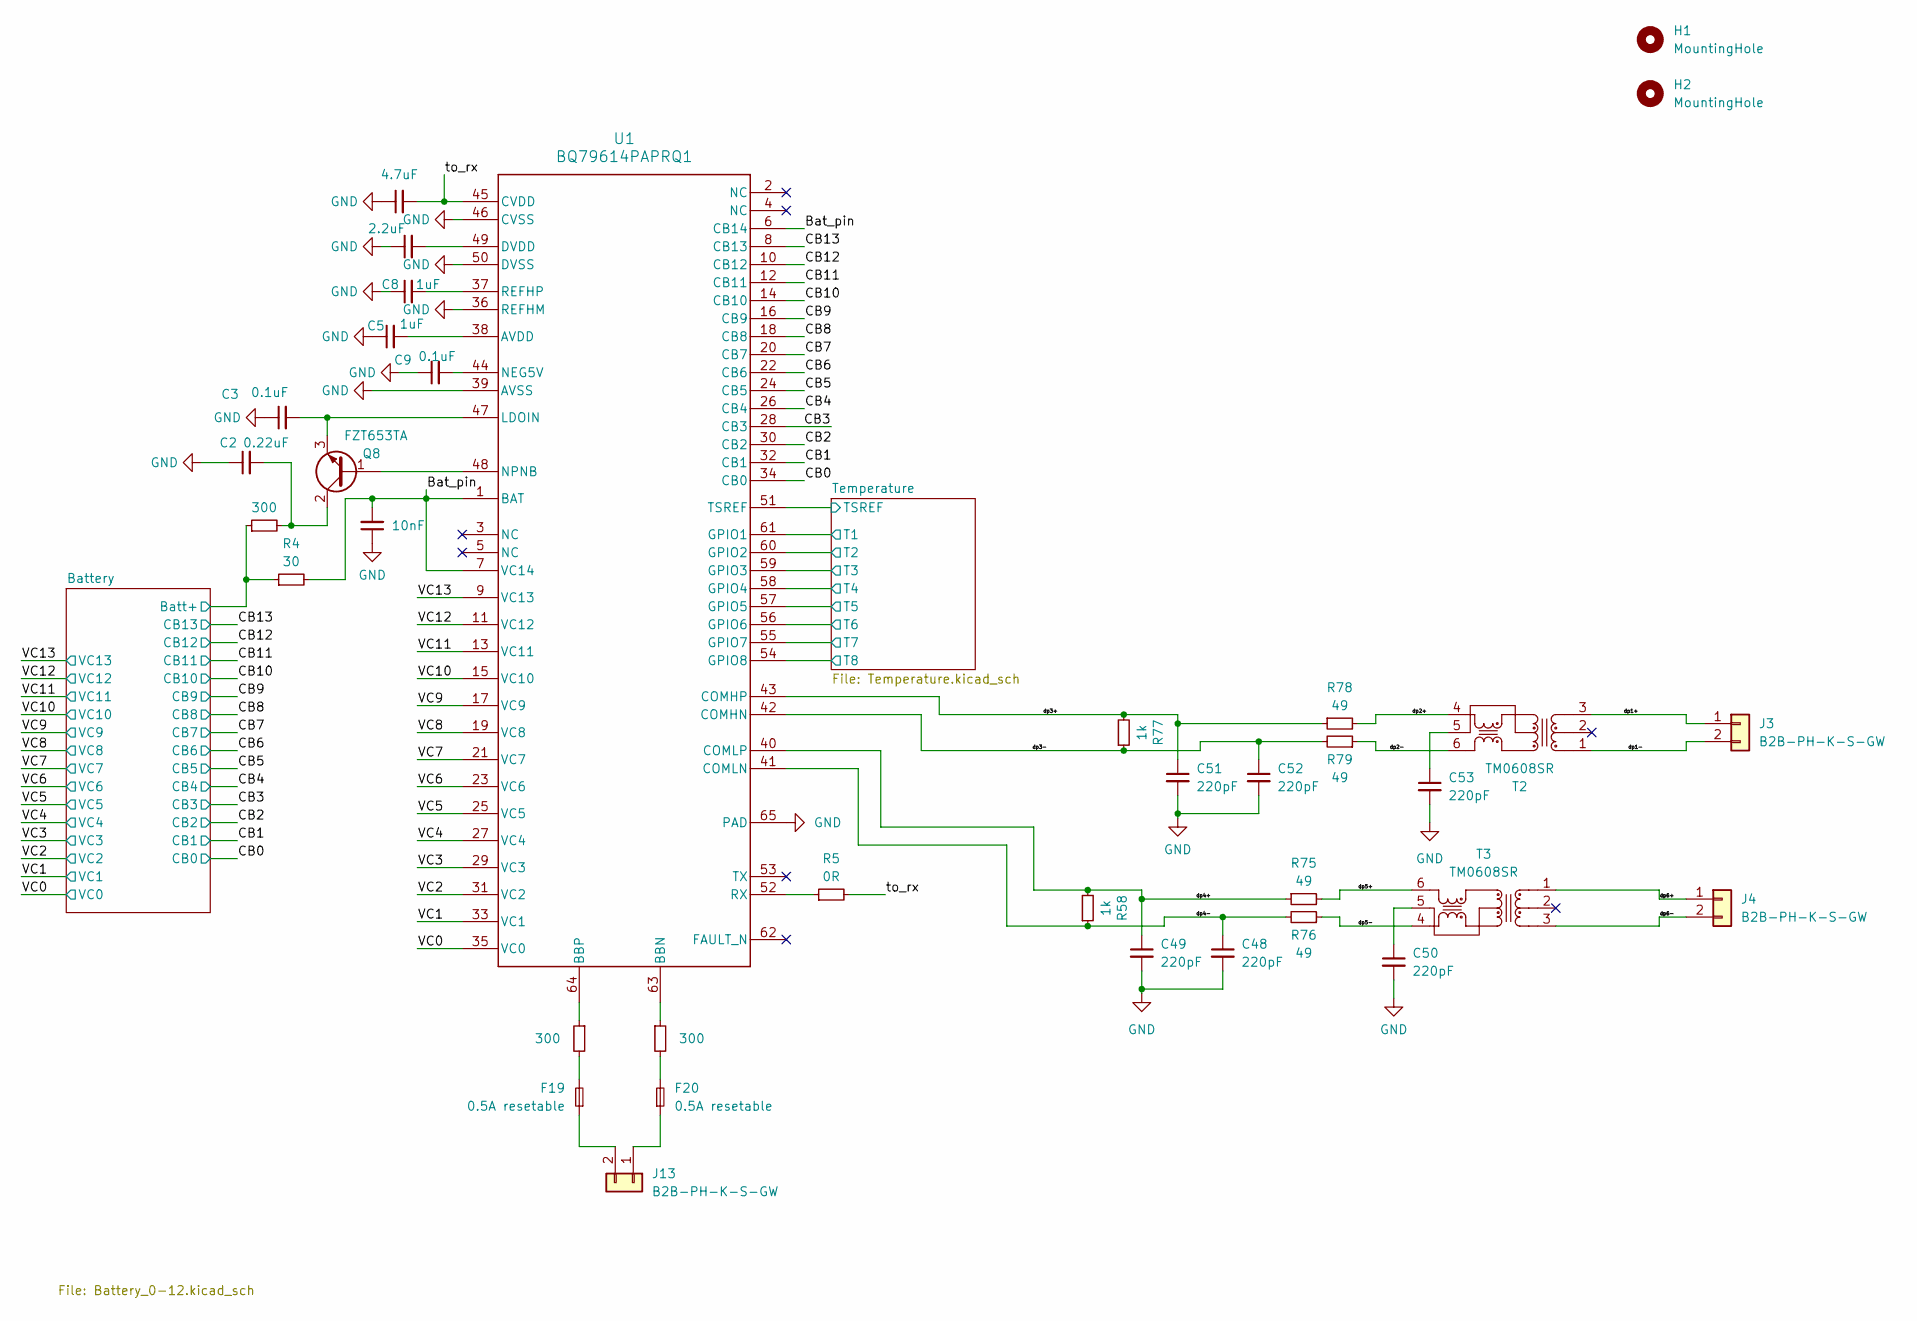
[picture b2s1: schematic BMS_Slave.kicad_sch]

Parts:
C2: 0.22uF; C_0805_2012Metric
C3, C9: 0.1uF; C_0603_1608Metric
C4: 10nF; C_0603_1608Metric_Pad1.08x0.95mm_HandSolder
C5, C8: 1uF; C_0805_2012Metric
C6: 4.7uF; C_0805_2012Metric
C7: 2.2uF; C_0805_2012Metric
C48, C49, C50, C51, C52, C53: 220pF; C_0603_1608Metric; Mouser Part Number 581-06033A221JAT2A
F19, F20: 0.5A resetable; Fuse_0805_2012Metric
H1, H2: MountingHole; MountingHole_3.2mm_M3_DIN965
J3, J4, J13: B2B-PH-K-S-GW; CONN2_B2B-PH-K-S_JST
Q8: FZT653TA; SOT-223-3_TabPin2; Mouser Part Number 522-FZT653TA
R2, R3, R6: 300; R_0603_1608Metric
R4: 30; R_0603_1608Metric
R5: 0R; R_0603_1608Metric
R58, R77: 1k; R_0603_1608Metric; Manufacturer_Part_Number RT0603FRE07330RL; Mouser Part Number --
R75, R76, R78, R79: 49; R_0603_1608Metric; Manufacturer_Part_Number RT0603FRE07330RL; Mouser Part Number 603-RT0603FRE07330RL
T2, T3: TM0608SR; IC6_SM91502ALA-E_BRN; Mouser Part Number 652-SM91502ALE
U1: BQ79614PAPRQ1; Texas_TQFP-64-1EP_10x10mm_P0.5mm_EP8x8mm_Mask4.44x4.44mm_Th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

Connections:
/Bat_pin: C4.2, R4.2, U1.1 (BAT), U1.6 (CB14), U1.7 (VC14)
/Battery/Batt+: R2.1, R4.1; also elsewhere on the board
/CB0: U1.34 (CB0); also elsewhere on the board
/CB1: U1.32 (CB1); also elsewhere on the board
/CB2: U1.30 (CB2); also elsewhere on the board
/CB3: U1.28 (CB3); also elsewhere on the board
/CB4: U1.26 (CB4); also elsewhere on the board
/CB5: U1.24 (CB5); also elsewhere on the board
/CB6: U1.22 (CB6); also elsewhere on the board
/CB7: U1.20 (CB7); also elsewhere on the board
/CB8: U1.18 (CB8); also elsewhere on the board
/CB9: U1.16 (CB9); also elsewhere on the board
/CB10: U1.14 (CB10); also elsewhere on the board
/CB11: U1.12 (CB11); also elsewhere on the board
/CB12: U1.10 (CB12); also elsewhere on the board
/CB13: U1.8 (CB13); also elsewhere on the board
/Temperature/T1: U1.61 (GPIO1); also elsewhere on the board
/Temperature/T2: U1.60 (GPIO2); also elsewhere on the board
/Temperature/T3: U1.59 (GPIO3); also elsewhere on the board
/Temperature/T4: U1.58 (GPIO4); also elsewhere on the board
/Temperature/T5: U1.57 (GPIO5); also elsewhere on the board
/Temperature/T6: U1.56 (GPIO6); also elsewhere on the board
/Temperature/T7: U1.55 (GPIO7); also elsewhere on the board
/Temperature/T8: U1.54 (GPIO8); also elsewhere on the board
/Temperature/TSREF: U1.51 (TSREF); also elsewhere on the board
/VC0: U1.35 (VC0); also elsewhere on the board
/VC1: U1.33 (VC1); also elsewhere on the board
/VC2: U1.31 (VC2); also elsewhere on the board
/VC3: U1.29 (VC3); also elsewhere on the board
/VC4: U1.27 (VC4); also elsewhere on the board
/VC5: U1.25 (VC5); also elsewhere on the board
/VC6: U1.23 (VC6); also elsewhere on the board
/VC7: U1.21 (VC7); also elsewhere on the board
/VC8: U1.19 (VC8); also elsewhere on the board
/VC9: U1.17 (VC9); also elsewhere on the board
/VC10: U1.15 (VC10); also elsewhere on the board
/VC11: U1.13 (VC11); also elsewhere on the board
/VC12: U1.11 (VC12); also elsewhere on the board
/VC13: U1.9 (VC13); also elsewhere on the board
/dp1+: J3.1, T2.3 (PRI_3)
/dp1-: J3.2, T2.1 (PRI_1)
/dp2+: R78.2, T2.4 (SEC_1)
/dp2-: R79.1, T2.6 (SEC_3)
/dp3+: C51.1, R77.2, R78.1, U1.43 (COMHP)
/dp3-: C52.1, R77.1, R79.2, U1.42 (COMHN)
/dp4+: C49.1, R58.2, R75.1, U1.40 (COMLP)
/dp4-: C48.1, R58.1, R76.2, U1.41 (COMLN)
/dp5+: R75.2, T3.6 (SEC_3)
/dp5-: R76.1, T3.4 (SEC_1)
/dp6+: J4.1, T3.1 (PRI_1)
/dp6-: J4.2, T3.3 (PRI_3)
/to_rx: C6.2, R5.2, U1.45 (CVDD)
GND: C2.1, C3.1, C4.1, C5.1, C6.1, C7.1, C8.1, C9.1, C48.2, C49.2, C50.2, C51.2, C52.2, C53.2, U1.36 (REFHM), U1.39 (AVSS), U1.46 (CVSS), U1.50 (DVSS), U1.65 (PAD); also elsewhere on the board
unnamed: F19.2, R3.2
unnamed: F20.2, R6.2
unnamed: F20.1, J13.1
unnamed: F19.1, J13.2
unnamed: Q8.1 (B), U1.48 (NPNB)
unnamed: C2.2, Q8.2 (C), R2.2
unnamed: C3.2, Q8.3 (E), U1.47 (LDOIN)
unnamed: C53.1, T2.5 (SEC_2)
unnamed: C50.1, T3.5 (SEC_2)
unnamed: C5.2, U1.38 (AVDD)
unnamed: R6.1, U1.63 (BBN)
unnamed: R3.1, U1.64 (BBP)
unnamed: C7.2, U1.49 (DVDD)
unnamed: C9.2, U1.44 (NEG5V)
unnamed: C8.2, U1.37 (REFHP)
unnamed: R5.1, U1.52 (RX)
